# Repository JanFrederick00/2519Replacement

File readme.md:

# Apple I 2519B replacement

This is my own version of the PCB for replacing the 2519 IC on the Apple 1 motherboard.

This is based on [this project](https://oshwlab.com/szillat/2519-fixed) and [this SMD version](https://www.applefritter.com/content/2519-smd-replacement).

The main difference between these and this one is that this PCB is soldered on the bottom of the Apple 1 motherboard, leaving the socket on top free for a dummy-ic or simply to leave it empty.

Disclaimer: I designed this PCB two years ago, and the layout might not be optimal.

## Pictures

## Installation

See the above picture for how the board attaches to the motherboard.

I recommend installing a machined pin socket into position C3 and soldering it in place.
Place the daughterboard on the bottom as shown such that the DIP footprint on the board are located on the solder joints of the socket.
Make sure the labeled pin numbers match the pins on the IC - remember that this is the bottom and so the numbering is flipped.

Add more solder to the DIP footprint to attach the daughterboard. I had my batch of PCBs manufactured at 0.8mm thickness (many PCB manufacturers can do this at no additional cost)
which might help with this step.

Add a small wire from a ground-pad of your choice (I used pin 1 of the IC at location D1) to the labelled GND-pad on the daughterboard.
Note that the wide trace running directly under the PCB at this location is not connected to GND, making it unsuitable for this purpose.
  
I used some wire-wrapping wire (30AWG) and routed it underneath the daughterboard (there is a small gap between the two PCBs). This prevents this wire from getting caught on anything.

If the wrong characters are shown on screen, refer to the character generator IC's character map to find which of the six shift registers is not working and check your solder joints for missing connections or bridges.

(I have written more about the build process of my own Apple 1 [here](https://www.applefritter.com/content/another-apple-1-lives))
## BOM

The PCB uses six MC14557B shift register ICs and a 100nF decoupling capacitor for each.

|Reference|Part No.|Link|
|---|---|---|
|U1,U2,U3,U4,U5,U6|MC14557B|https://eu.mouser.com/ProductDetail/onsemi/MC14557BDWR2G?qs=g2rIOKKlpobUZ7ljsbuxeQ%3D%3D|
|C1,C2,C3,C4,C5,C6|Ceramic Capacitor 16V 0805 0.1uF|generic|

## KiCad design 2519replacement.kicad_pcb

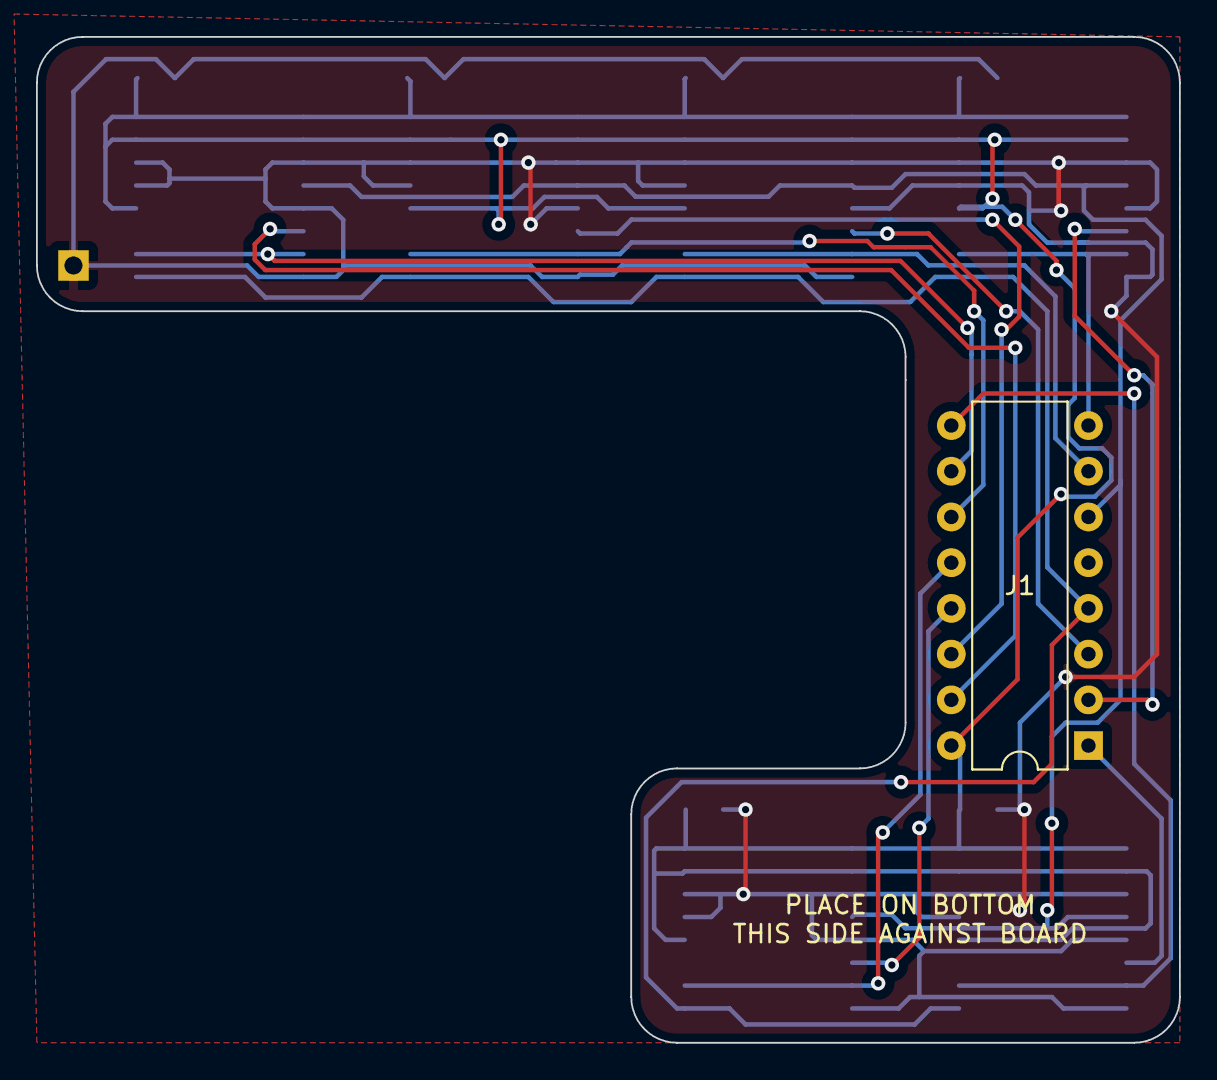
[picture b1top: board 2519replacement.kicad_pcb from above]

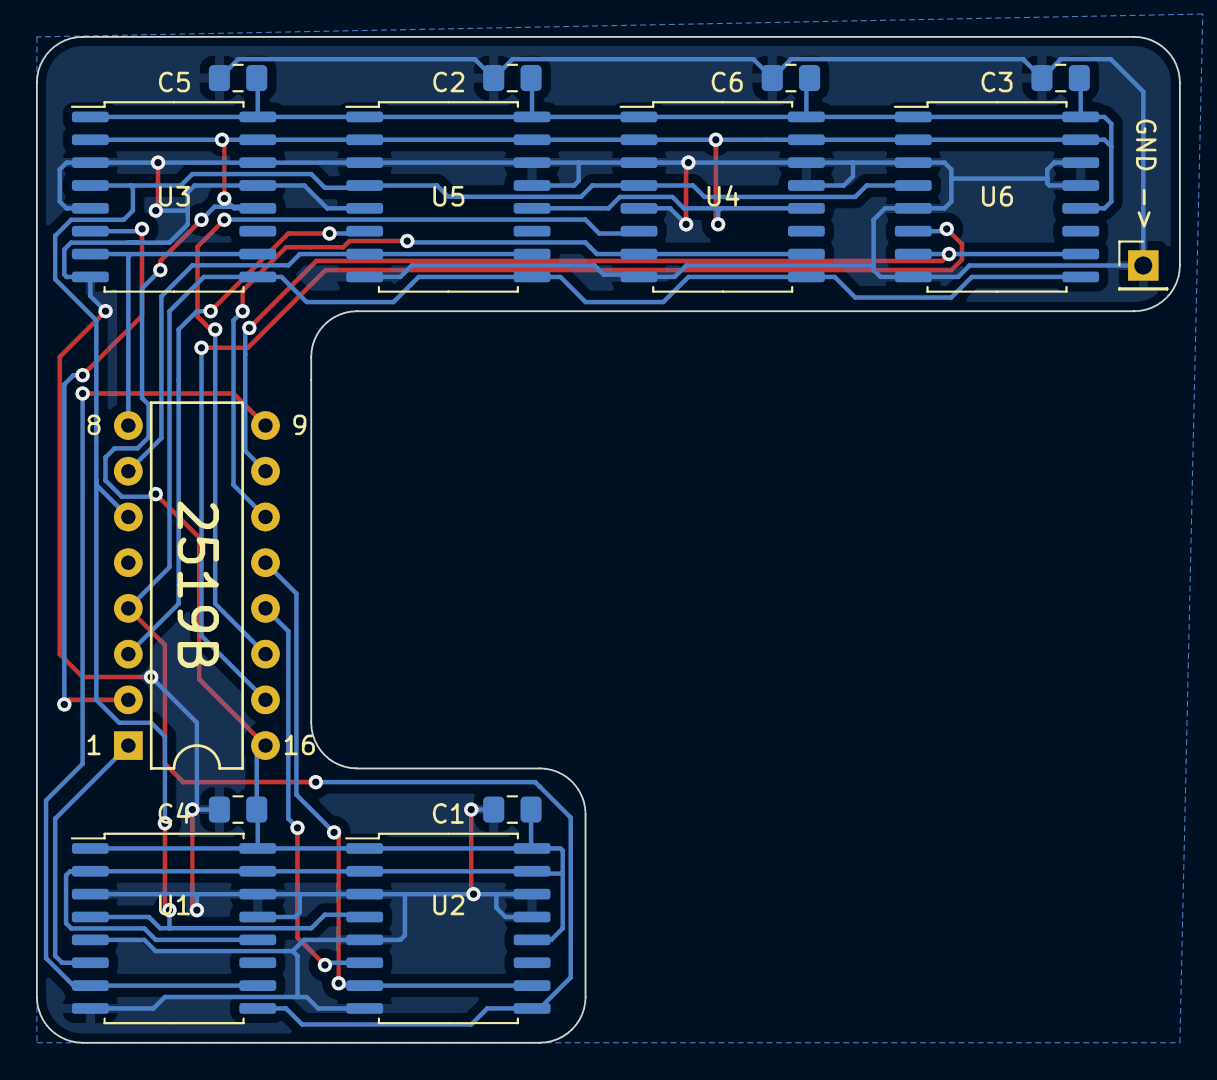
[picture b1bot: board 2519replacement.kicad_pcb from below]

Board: 2 copper layers, 63.5 x 55.9 mm, 14 parts (13 on the bottom side), 16 nets.

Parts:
C1, C2, C3, C4, C5, C6: 100n; C_0805_2012Metric_Pad1.18x1.45mm_HandSolder
J1: 2519b; DIP-16_W7.62mm
J2: GND; PinHeader_1x01_P2.54mm_Vertical
U1, U2, U3, U4, U5, U6: MC14557B; SOIC-16W_7.5x10.3mm_P1.27mm

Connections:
+5V: C1.1, C2.1, C3.1, C4.1, C5.1, C6.1, J1.16, U1.1 (L2), U1.2 (L1), U1.12 (L32), U1.15 (L4), U1.16 (Vdd), U2.1 (L2), U2.2 (L1), U2.12 (L32), U2.15 (L4), U2.16 (Vdd), U3.1 (L2), U3.2 (L1), U3.12 (L32), U3.15 (L4), U3.16 (Vdd), U4.1 (L2), U4.2 (L1), U4.12 (L32), U4.15 (L4), U4.16 (Vdd), U5.1 (L2), U5.2 (L1), U5.12 (L32), U5.15 (L4), U5.16 (Vdd), U6.1 (L2), U6.2 (L1), U6.12 (L32), U6.15 (L4), U6.16 (Vdd)
/A/B: J1.4, U1.9 (A/B_SEL), U2.9 (A/B_SEL), U3.9 (A/B_SEL), U4.9 (A/B_SEL), U5.9 (A/B_SEL), U6.9 (A/B_SEL)
/CLK: J1.6, U1.4 (CLOCK), U2.4 (CLOCK), U3.4 (CLOCK), U4.4 (CLOCK), U5.4 (CLOCK), U6.4 (CLOCK)
GND: C1.2, C2.2, C3.2, C4.2, C5.2, C6.2, J2.1, U1.3 (RESET), U1.5 (~CE), U1.8 (Vss), U1.13 (L16), U1.14 (L8), U2.3 (RESET), U2.5 (~CE), U2.8 (Vss), U2.13 (L16), U2.14 (L8), U3.3 (RESET), U3.5 (~CE), U3.8 (Vss), U3.13 (L16), U3.14 (L8), U4.3 (RESET), U4.5 (~CE), U4.8 (Vss), U4.13 (L16), U4.14 (L8), U5.3 (RESET), U5.5 (~CE), U5.8 (Vss), U5.13 (L16), U5.14 (L8), U6.3 (RESET), U6.5 (~CE), U6.8 (Vss), U6.13 (L16), U6.14 (L8)
unnamed: J1.1, U1.6 (B)
unnamed: J1.2, U3.6 (B)
unnamed: J1.3, U5.6 (B)
unnamed: J1.7, U5.7 (A), U5.10 (Q)
unnamed: J1.8, U3.7 (A), U3.10 (Q)
unnamed: J1.9, U1.7 (A), U1.10 (Q)
unnamed: J1.10, U6.7 (A), U6.10 (Q)
unnamed: J1.11, U4.7 (A), U4.10 (Q)
unnamed: J1.12, U2.7 (A), U2.10 (Q)
unnamed: J1.13, U2.6 (B)
unnamed: J1.14, U4.6 (B)
unnamed: J1.15, U6.6 (B)

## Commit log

2025-05-02 initial version
